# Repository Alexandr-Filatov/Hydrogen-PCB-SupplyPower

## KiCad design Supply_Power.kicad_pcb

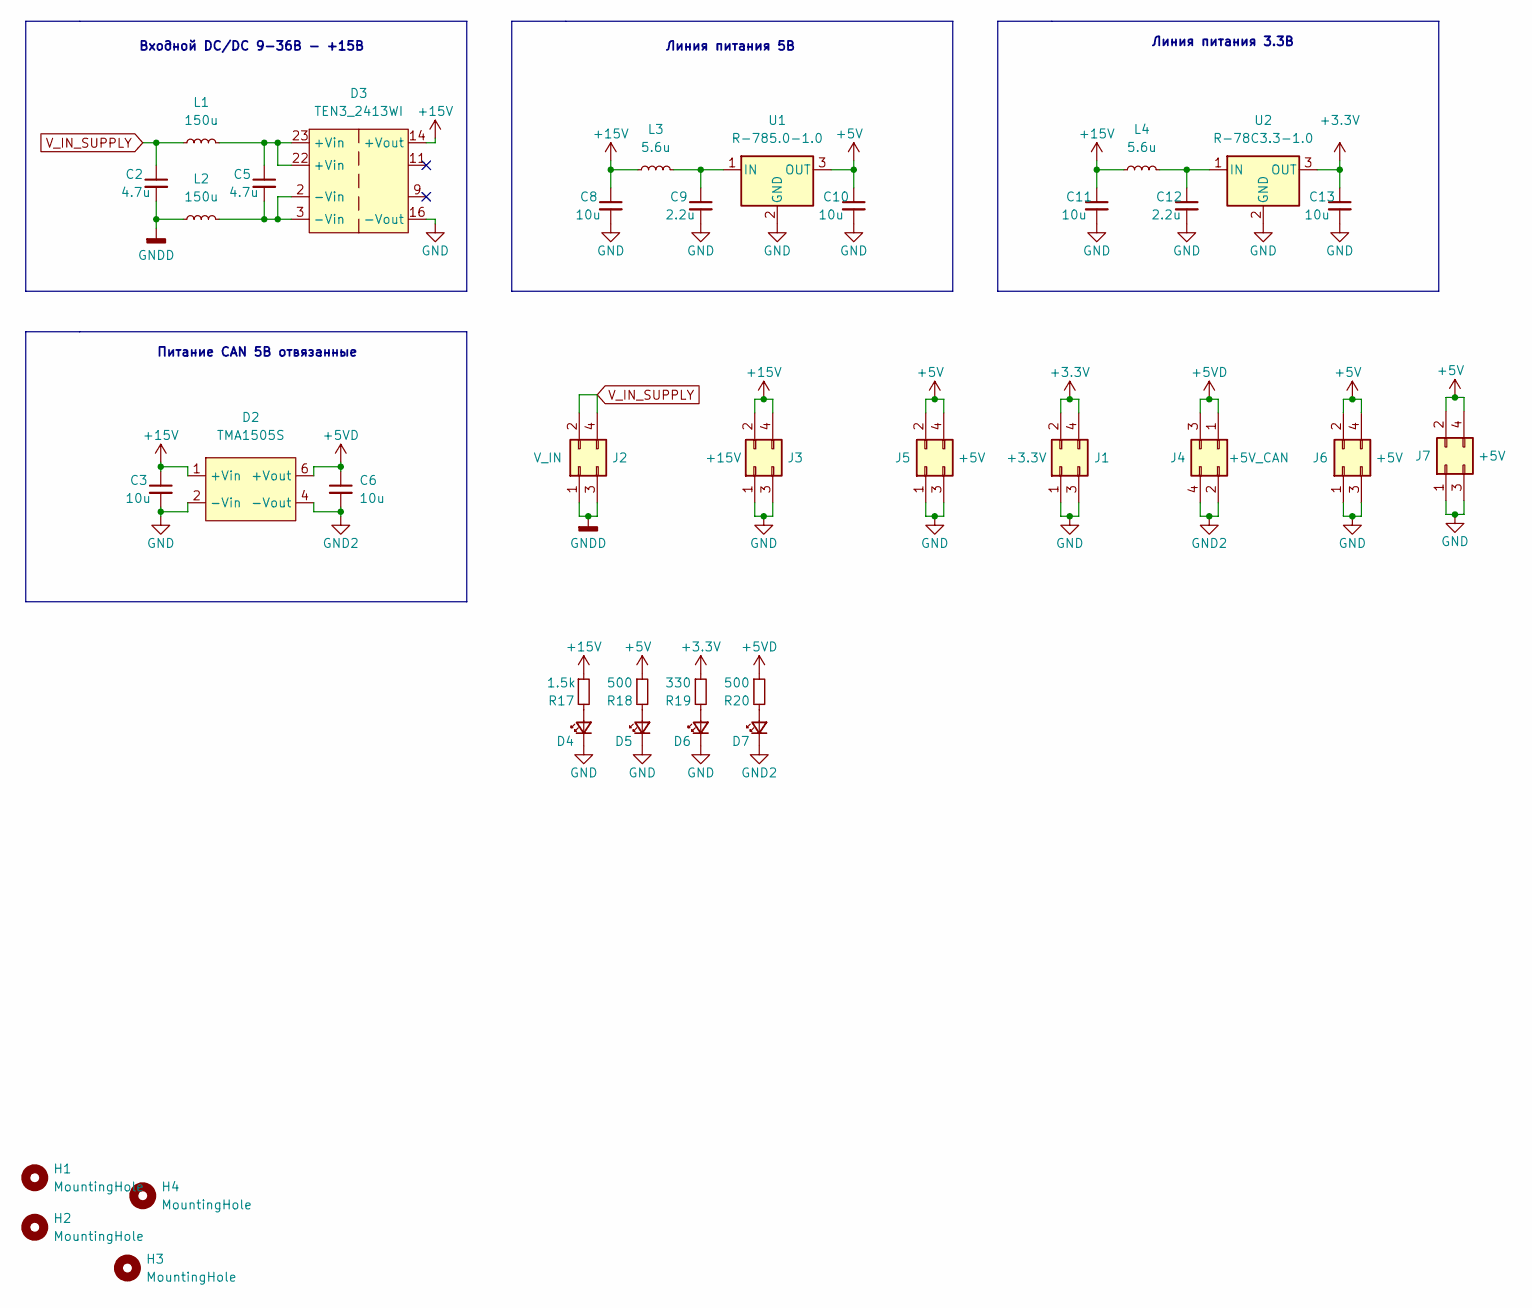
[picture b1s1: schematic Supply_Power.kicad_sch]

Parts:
C2, C5: 4.7u; C_1210_3225Metric_Pad1.33x2.70mm_HandSolder
C3, C6, C8, C10, C11, C13: 10u; C_1210_3225Metric_Pad1.33x2.70mm_HandSolder
C9, C12: 2.2u; C_1210_3225Metric_Pad1.33x2.70mm_HandSolder
D2: TMA1505S
D3: TEN3_2413WI; TEN3_2413
D4: +15V; LED_0805_2012Metric_Pad1.15x1.40mm_HandSolder
D5: +5V; LED_0805_2012Metric_Pad1.15x1.40mm_HandSolder
D6: 3.3V; LED_0805_2012Metric_Pad1.15x1.40mm_HandSolder
D7: +5V_CAN; LED_0805_2012Metric_Pad1.15x1.40mm_HandSolder
H1, H2, H3, H4: MountingHole; MountingHole_3.2mm_M3
J1: +3.3V; Molex_Micro-Fit_3.0_43045-0400_2x02_P3.00mm_Horizontal
J2: V_IN; Molex_Micro-Fit_3.0_43045-0400_2x02_P3.00mm_Horizontal
J3: +15V; Molex_Micro-Fit_3.0_43045-0400_2x02_P3.00mm_Horizontal
J4: +5V_CAN; Molex_Micro-Fit_3.0_43045-0400_2x02_P3.00mm_Horizontal
J5, J6, J7: +5V; Molex_Micro-Fit_3.0_43045-0400_2x02_P3.00mm_Horizontal
L1, L2: 150u; L_1812_4532Metric_Pad1.30x3.40mm_HandSolder
L3, L4: 5.6u; L_1210_3225Metric_Pad1.42x2.65mm_HandSolder
R17: 1.5k; R_0805_2012Metric_Pad1.20x1.40mm_HandSolder
R18, R20: 500; R_0805_2012Metric_Pad1.20x1.40mm_HandSolder
R19: 330; R_0805_2012Metric_Pad1.20x1.40mm_HandSolder
U1: R-785.0-1.0; Converter_DCDC_RECOM_R-78E-0.5_THT
U2: R-78C3.3-1.0; Converter_DCDC_RECOM_R-78E-0.5_THT

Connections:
+3V3: C13.1, J1.2, J1.4, R19.1, U2.3 (OUT)
+5V: C10.1, J5.2, J5.4, J6.2, J6.4, J7.2, J7.4, R18.1, U1.3 (OUT)
+5VD: C6.1, D2.6 (+Vout), J4.1, J4.3, R20.1
+15V: C3.1, C8.1, C11.1, D2.1 (+Vin), D3.14 (+Vout), J3.2, J3.4, L3.1, L4.1, R17.1
GND: C3.2, C8.2, C9.2, C10.2, C11.2, C12.2, C13.2, D2.2 (-Vin), D3.16 (-Vout), D4.1 (K), D5.1 (K), D6.1 (K), J1.1, J1.3, J3.1, J3.3, J5.1, J5.3, J6.1, J6.3, J7.1, J7.3, U1.2 (GND), U2.2 (GND)
GND2: C6.2, D2.4 (-Vout), D7.1 (K), J4.2, J4.4
GNDD: C2.2, J2.1, J2.3, L2.1
unnamed: C5.1, D3.22 (+Vin), D3.23 (+Vin), L1.2
unnamed: C5.2, D3.2 (-Vin), D3.3 (-Vin), L2.2
unnamed: C9.1, L3.2, U1.1 (IN)
unnamed: C12.1, L4.2, U2.1 (IN)
unnamed: D4.2 (A), R17.2
unnamed: D5.2 (A), R18.2
unnamed: D6.2 (A), R19.2
unnamed: D7.2 (A), R20.2
V_IN_SUPPLY: C2.1, J2.2, J2.4, L1.1

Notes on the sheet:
Питание CAN 5В отвязанные
Входной DC/DC 9-36В - +15В
Линия питания 3.3В
Линия питания 5В

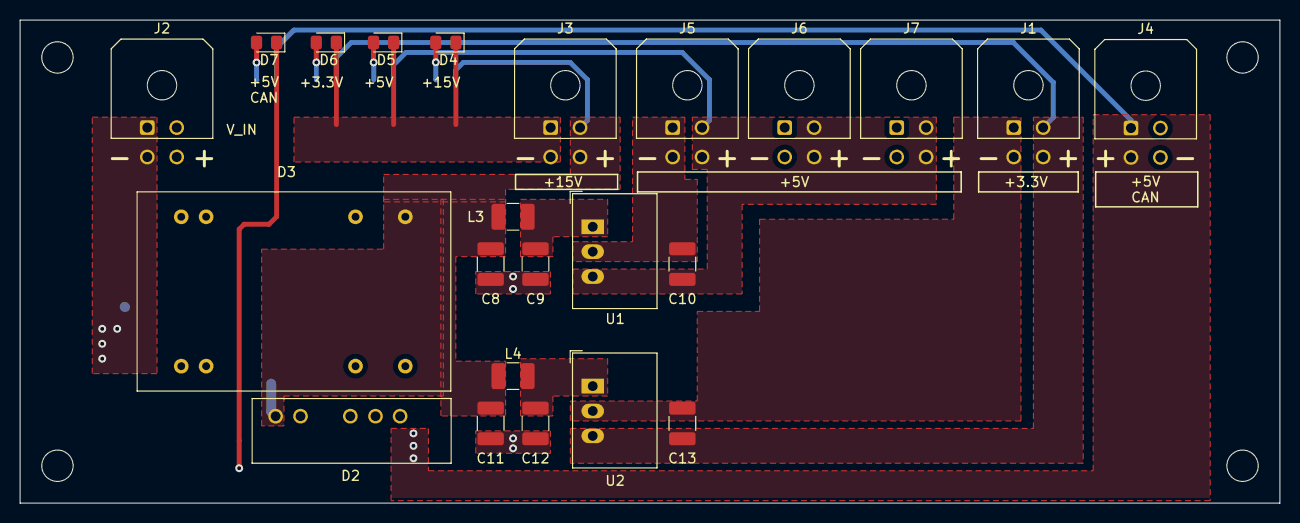
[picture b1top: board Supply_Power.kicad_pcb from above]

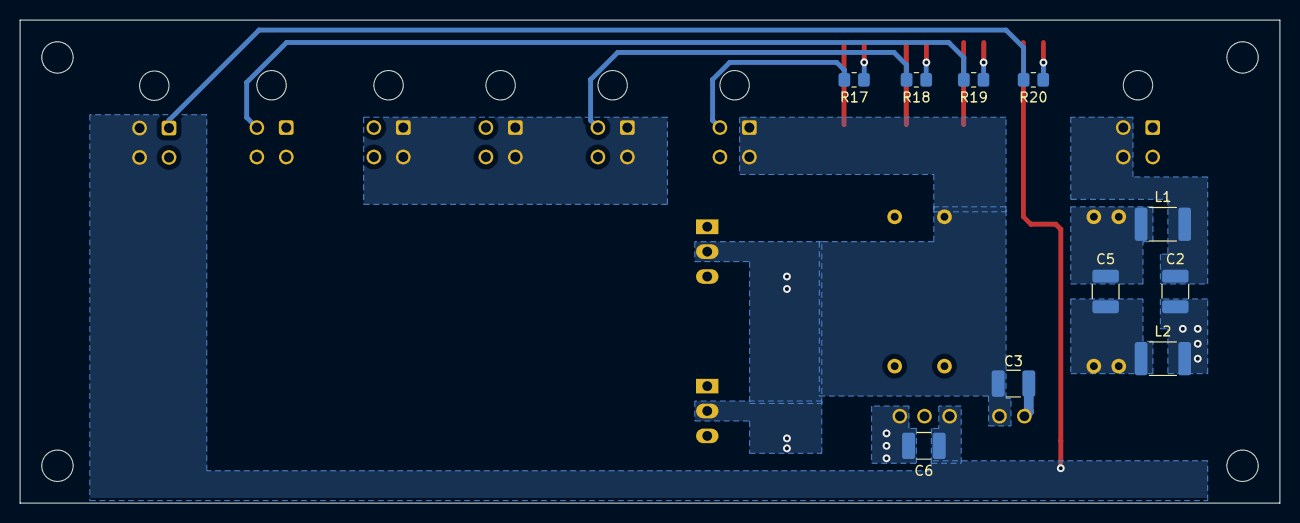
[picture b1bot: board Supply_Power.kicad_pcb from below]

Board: 2 copper layers, 128.5 x 49.3 mm, 37 parts (10 on the bottom side), 16 nets.

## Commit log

2022-05-26 VER1.0
2022-06-02 Первая версия в производство
